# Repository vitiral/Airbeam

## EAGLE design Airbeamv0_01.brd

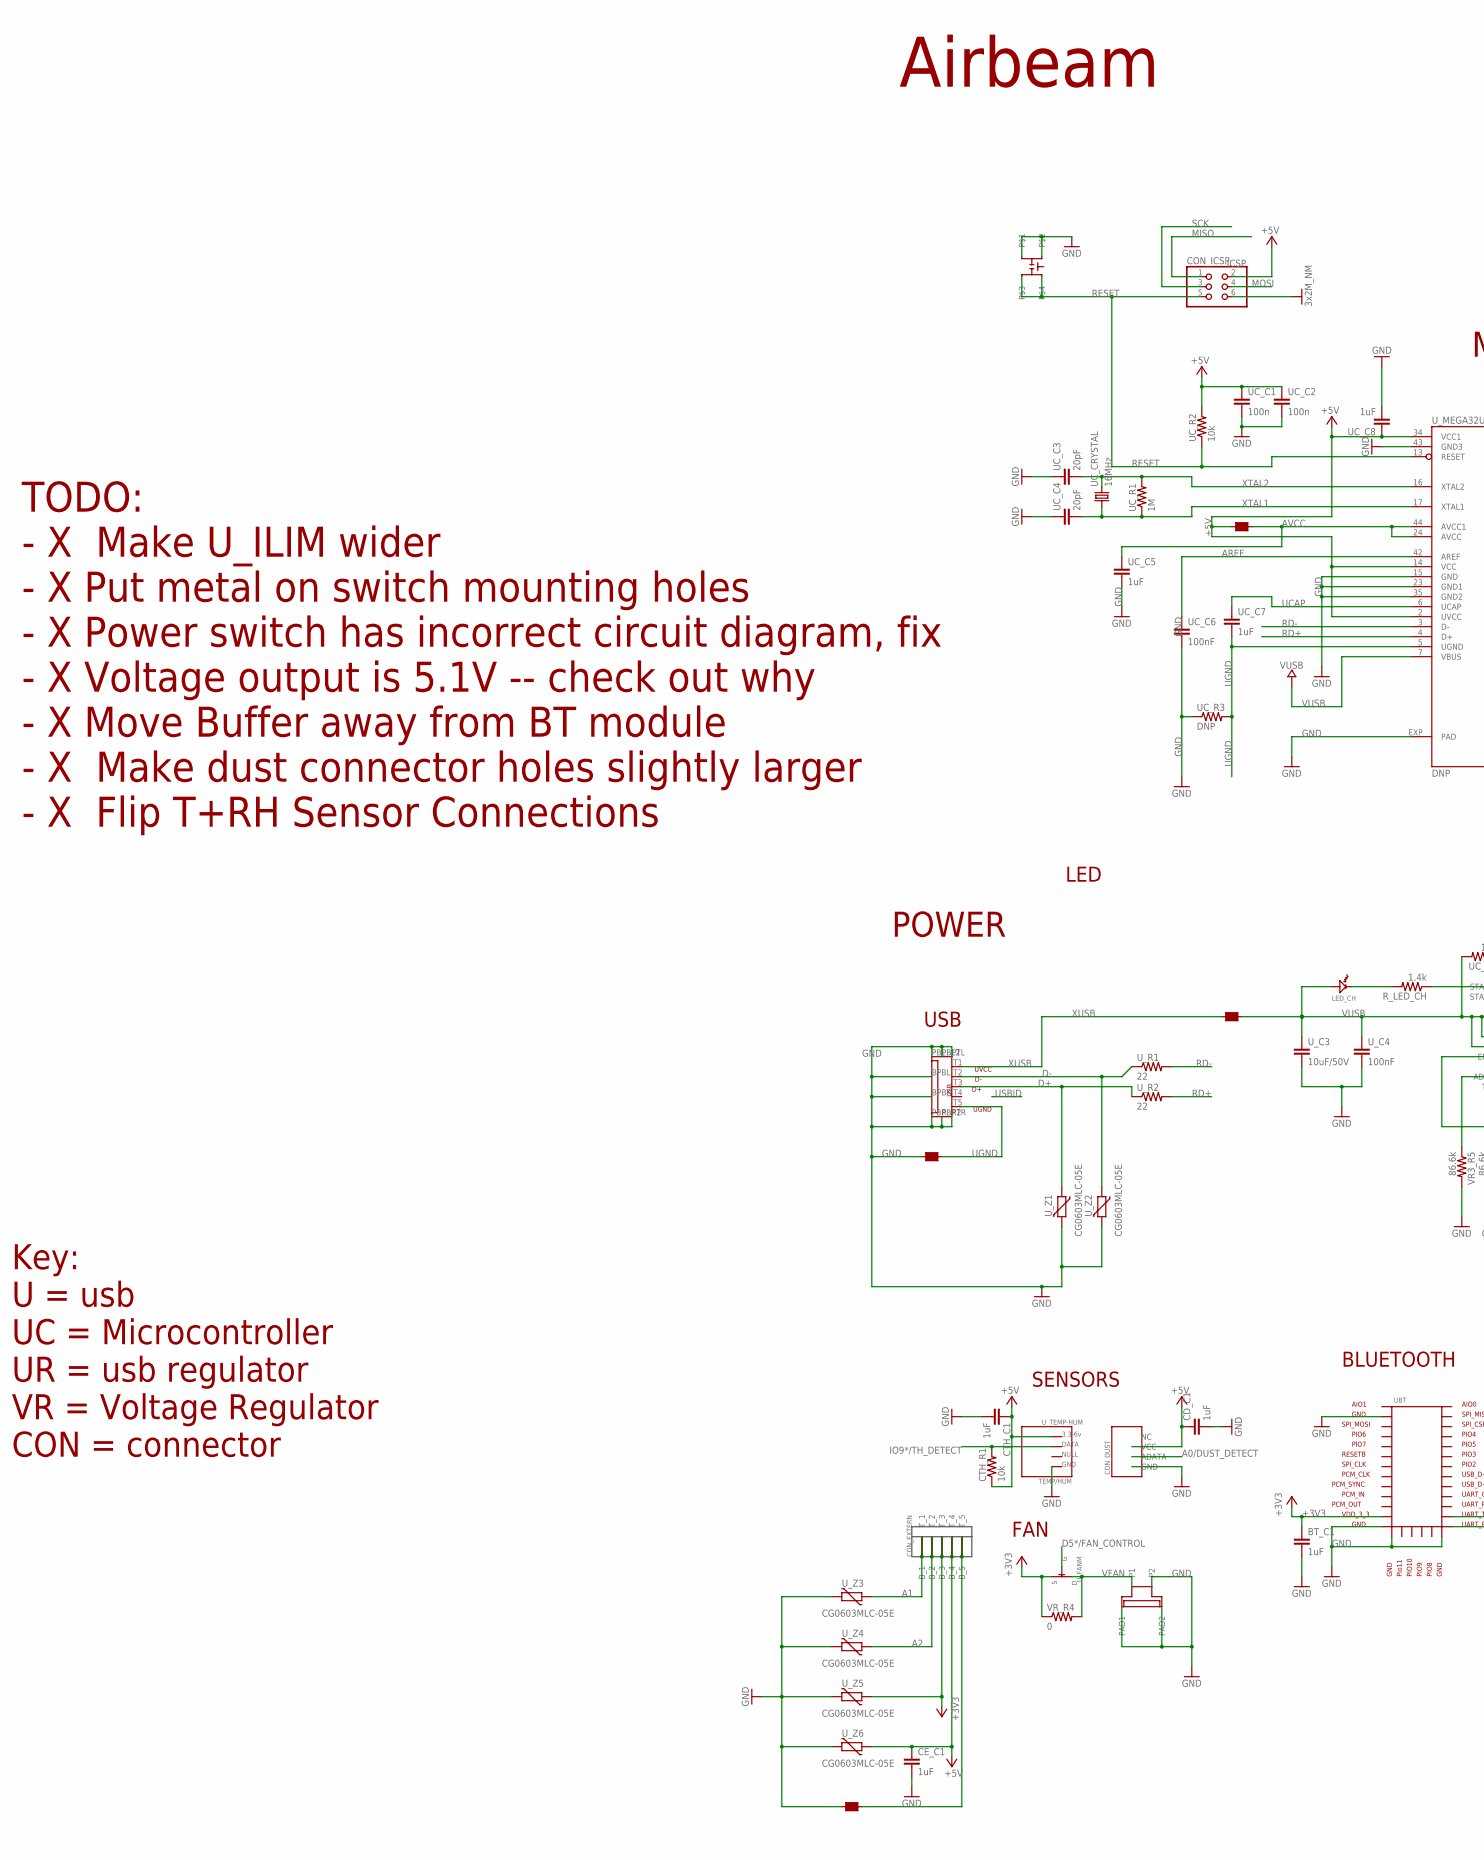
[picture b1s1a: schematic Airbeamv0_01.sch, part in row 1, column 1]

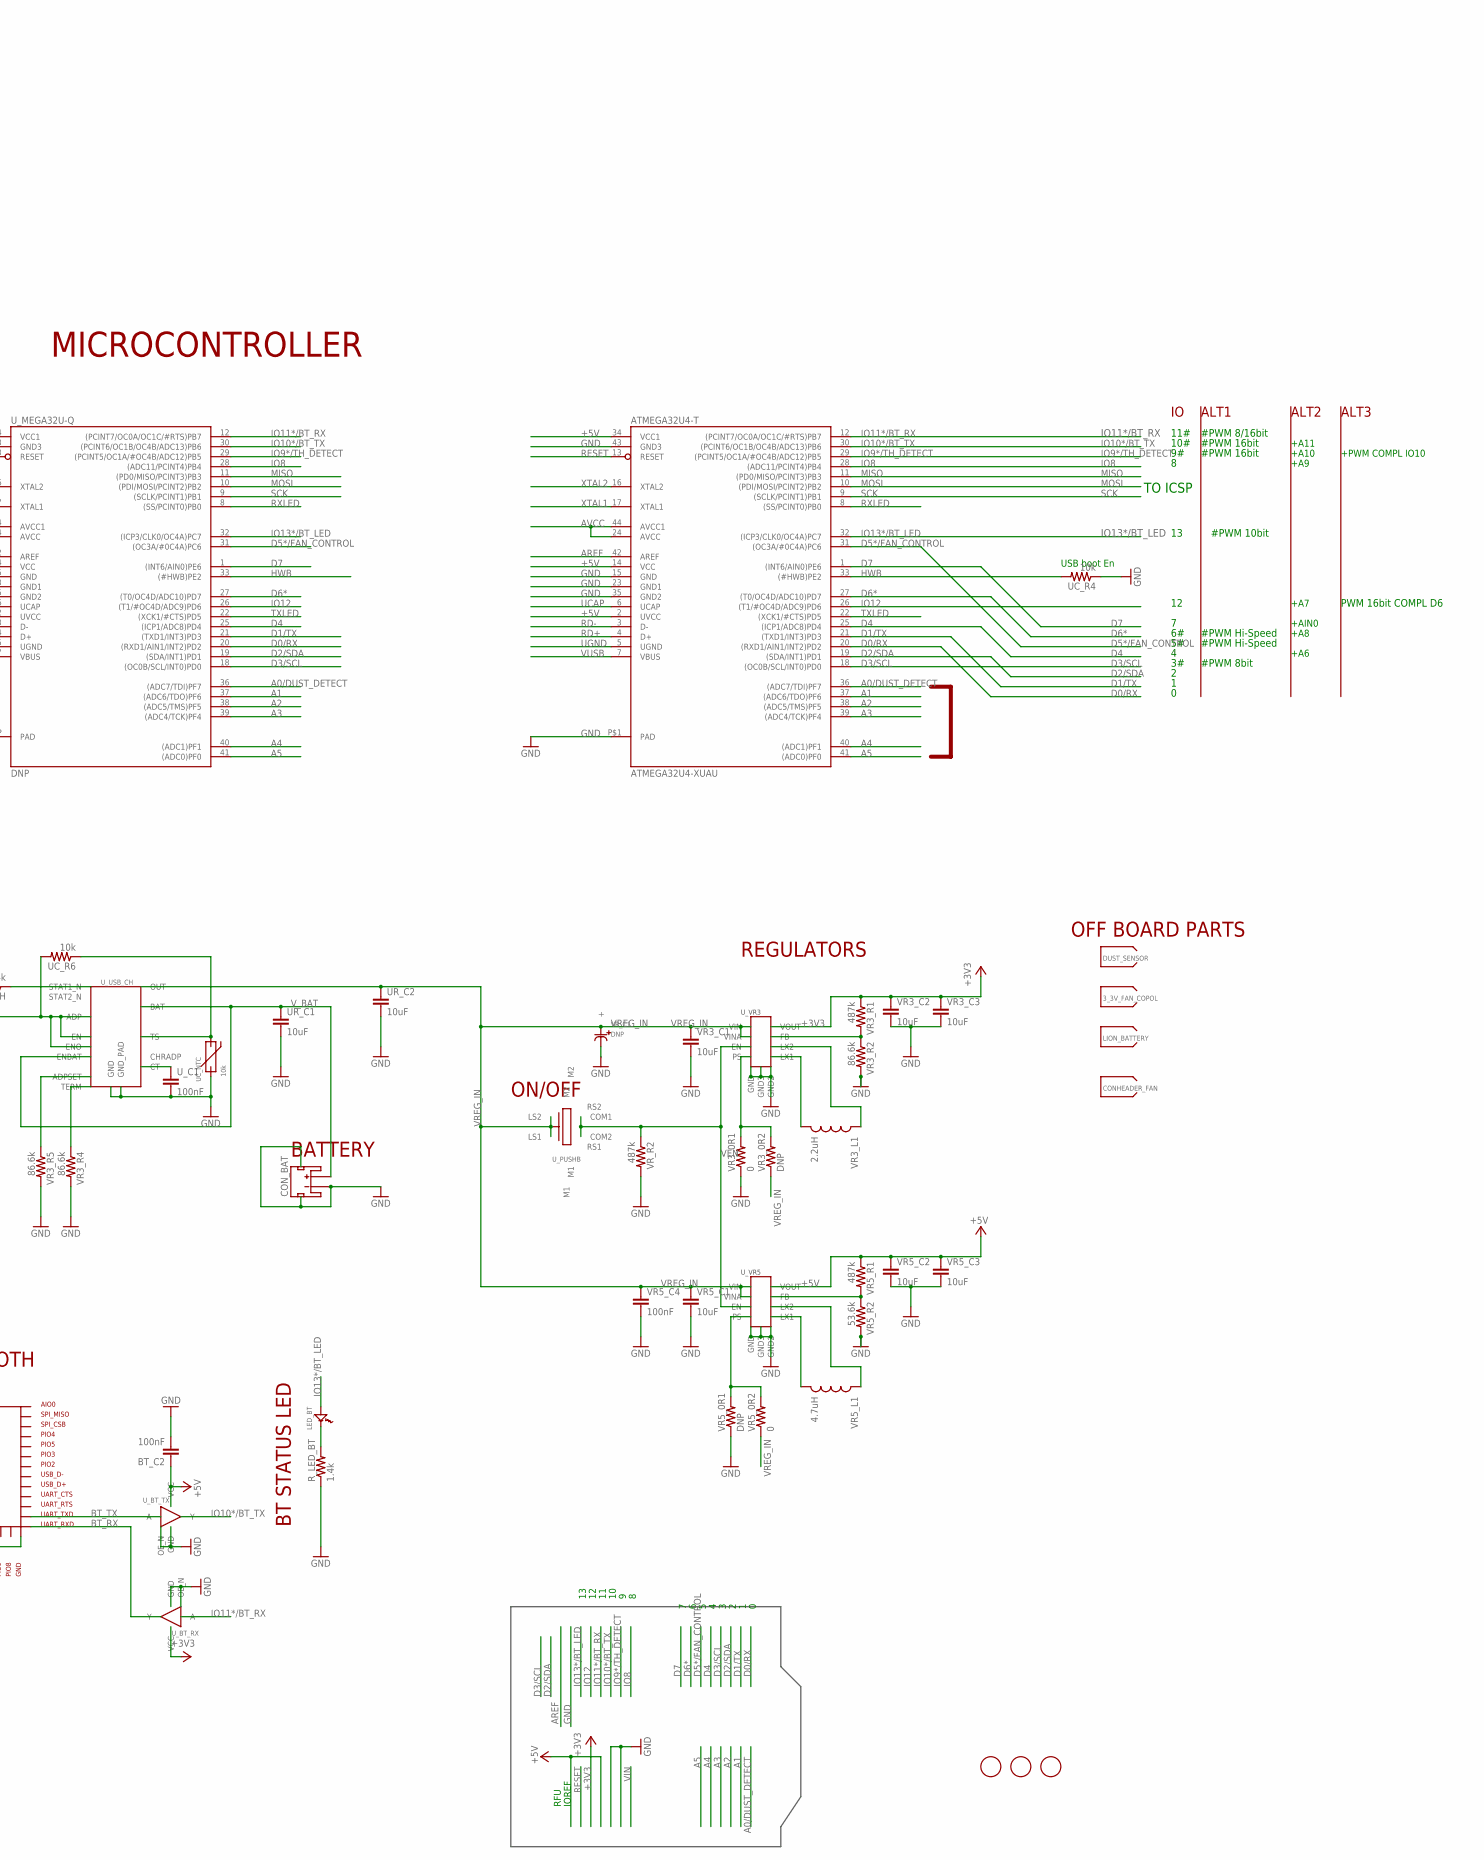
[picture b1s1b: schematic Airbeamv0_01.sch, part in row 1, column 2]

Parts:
3_3V_FAN_COPOL: OFF_BOARD; EMPTY; PARTNO F16FB-05LLC/E
ATMEGA32U4-T: ATMEGA32U4-XUAU; TQFP44-PAD; PARTNO ATMEGA32U4-AU
BT_C1: 1uF; 0603-CAP; PARTNO C1608X5R1C105K080AA
BT_C2: 100nF; 0603-CAP; PARTNO C1608X7R1E104K080AA
CA_FB1: FERITE_BEAD; U_FB1; PARTNO MH2029-600Y
CD_C1: 1uF; 0603-CAP; PARTNO C1608X5R1C105K080AA
CE_C1: 1uF; 0603-CAP; PARTNO C1608X5R1C105K080AA
CONHEADER_FAN: OFF_BOARD; EMPTY; PARTNO 02SUR-32S
CON_BAT: CON_BAT; JST-2-SMD; PARTNO S2B-PH-SM4-TB(LF)(SN)
CON_DUST: CON_DUST; S4B-EH; PARTNO S4B-EH
CON_EXTERN: TBLOCK_5; PARTNO 1770911
CON_FAN: SUR_2PIN; JST-0.8MM
CON_ICSP: ICSP; 2X03; PARTNO 67997-206HLF
CON_USB: USB-FCI
CTH_C1: 1uF; 0603-CAP; PARTNO C1608X5R1C105K080AA
CTH_R1: 10k; 0603-RES; PARTNO RC0603JR-0710KL
DUST_SENSOR: OFF_BOARD; EMPTY; PARTNO PPD60PV-T2
FID1, FID2, FID3: FIDUCIALMOUNT; FIDUCIA-MOUNT; PARTNO DNP
LED_BT: LED; LED_550; PARTNO 550-1107F
LED_CH: LED; LED_550; PARTNO 550-1307F
LION_BATTERY: OFF_BOARD; EMPTY; PARTNO 585460_2000mAh
RESET_SWITCH: DNP; SWITCH_TACTILE
R_LED_BT: 1.4k; 0603-RES; PARTNO RC0603FR-071K4L
R_LED_CH: 1.4k; 0603-RES; PARTNO RC0603FR-071K4L
UBT: BT-NVC-MDCS42A; BT_NVC-MDCS42A
UC_C1, UC_C2: 100n; 0603-CAP; PARTNO C1608X7R1E104K080AA
UC_C3, UC_C4: 20pF; 0603-CAP; PARTNO CL10C200JB8NNNC
UC_C5, UC_C7, UC_C8: 1uF; 0603-CAP; PARTNO C1608X5R1C105K080AA
UC_C6: 100nF; 0603-CAP; PARTNO C1608X7R1E104K080AA
UC_CRYSTAL: 16MHz; HC49UP; PARTNO ECS-160-20-3X-TR
UC_NTC: 10k; 0402; PARTNO ERT-J0EM103J
UC_R1: 1M; 0603-RES; PARTNO RC0603FR-071ML
UC_R2, UC_R4, UC_R6: 10k; 0603-RES; PARTNO RC0603JR-0710KL
UC_R3: DNP; 0603-RES; PARTNO RC0603JR-070RL
UR_C1, UR_C2: 10uF; 0805; PARTNO C2012X5R1C106K085AC
U_BT_RX: V_BUFFER; SOT23-5
U_BT_TX: V_BUFFER; SOT23-5
U_C1: 100nF; 0603-CAP; PARTNO C1608X7R1E104K080AA
U_C3: 10uF/50V; 1206; PARTNO CL31A106KBHNNNE
U_C4: 100nF; 0603-CAP; PARTNO CC0603ZRY5V9BB104
U_FANM: DNP; SOT23
U_FB1, U_FB2, U_FB3: FERITE_BEAD; U_FB1; PARTNO MH2029-600Y
U_MEGA32U-Q: DNP; QFN44ML7X7; PARTNO ATMEGA32U4-MU
U_PUSHB: PUSHBUTTON
U_R1, U_R2: 22; 0603-RES; PARTNO RC0603JR-0722RL
U_TEMP-HUM: RHT03
U_USB_CH: USB-BATTERY_LOAD; TDFN33-14; PARTNO AAT3672IWO-4.2-1-T1
U_VR3, U_VR5: VREG-RTEC6150; WFDFN-10
U_Z1, U_Z2, U_Z3, U_Z4, U_Z5, U_Z6: CG0603MLC-05E; CT/CN0603; PARTNO CG0603MLC-05E
VR3_0R1, VR5_0R2: 0; 0603-RES; PARTNO RC0603JR-070RL
VR3_0R2, VR5_0R1: DNP; 0603-RES; PARTNO RC0603JR-070RL
VR3_C1, VR3_C2, VR3_C3, VR5_C1, VR5_C2, VR5_C3: 10uF; 0805; PARTNO C2012X5R1C106K085AC
VR3_L1: 2.2uH; 1210; PARTNO BRL3225T2R2M
VR3_R1, VR5_R1: 487k; 0603-RES; PARTNO ERJ-3EKF4873V
VR3_R2, VR3_R4, VR3_R5: 86.6k; 0603-RES; PARTNO ERJ-3EKF8662V
VR5_C4: 100nF; 0603-CAP; PARTNO C1608X7R1E104K080AA
VR5_L1: 4.7uH; 1210; PARTNO CBC3225T4R7MR
VR5_R2: 53.6k; 0603-RES; PARTNO RC0805FR-0753K6L
VR_C1: DNP; 2917_CAP
VR_R2: 487k; 0603-RES; PARTNO ERJ-3EKF4873V
VR_R4: 0; 0603-RES; PARTNO RC0603JR-070RL

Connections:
+3V3: BT_C1.1, CON_EXTERN.B_3, CON_EXTERN.T_3, UBT.P$12, U_BT_RX.5 (VCC), U_FANM.2, U_VR3.P$1 (VOUT), U_Z5.1, VR3_C2.1, VR3_C3.1, VR3_R1.1, VR_R4.1
+5V: ATMEGA32U4-T.2 (UVCC), ATMEGA32U4-T.14 (VCC), ATMEGA32U4-T.34 (VCC1), BT_C2.1, CD_C1.1, CE_C1.1, CON_DUST.P$3 (VCC), CON_EXTERN.B_4, CON_EXTERN.T_4, CON_ICSP.2, CTH_C1.1, CTH_R1.1, UC_C1.1, UC_C2.1, UC_C8.1, UC_R2.2, U_BT_TX.5 (VCC), U_FB2.P$1, U_MEGA32U-Q.2 (UVCC), U_MEGA32U-Q.14 (VCC), U_MEGA32U-Q.34 (VCC1), U_TEMP-HUM.P$1, U_VR5.P$1 (VOUT), U_Z6.1, VR5_C2.1, VR5_C3.1, VR5_R1.1
A0/DUST_DETECT: ATMEGA32U4-T.36 ((ADC7/TDI)PF7), CON_DUST.P$2 (ADATA), U_MEGA32U-Q.36 ((ADC7/TDI)PF7)
A1: ATMEGA32U4-T.37 ((ADC6/TDO)PF6), CON_EXTERN.B_1, CON_EXTERN.T_1, U_MEGA32U-Q.37 ((ADC6/TDO)PF6), U_Z3.1
A2: ATMEGA32U4-T.38 ((ADC5/TMS)PF5), CON_EXTERN.B_2, CON_EXTERN.T_2, U_MEGA32U-Q.38 ((ADC5/TMS)PF5), U_Z4.1
A3: ATMEGA32U4-T.39 ((ADC4/TCK)PF4), U_MEGA32U-Q.39 ((ADC4/TCK)PF4)
A4: ATMEGA32U4-T.40 ((ADC1)PF1), U_MEGA32U-Q.40 ((ADC1)PF1)
A5: ATMEGA32U4-T.41 ((ADC0)PF0), U_MEGA32U-Q.41 ((ADC0)PF0)
AREF: ATMEGA32U4-T.42 (AREF), UC_C6.1, U_MEGA32U-Q.42 (AREF)
AVCC: ATMEGA32U4-T.24 (AVCC), ATMEGA32U4-T.44 (AVCC1), UC_C5.1, U_FB2.P$2, U_MEGA32U-Q.24 (AVCC), U_MEGA32U-Q.44 (AVCC1)
BT_RX: UBT.P$20, U_BT_RX.4 (Y)
BT_TX: UBT.P$21, U_BT_TX.2 (A)
D0/RX: ATMEGA32U4-T.20 ((RXD1/AIN1/INT2)PD2), U_MEGA32U-Q.20 ((RXD1/AIN1/INT2)PD2)
D1/TX: ATMEGA32U4-T.21 ((TXD1/INT3)PD3), U_MEGA32U-Q.21 ((TXD1/INT3)PD3)
D2/SDA: ATMEGA32U4-T.19 ((SDA/INT1)PD1), U_MEGA32U-Q.19 ((SDA/INT1)PD1)
D3/SCL: ATMEGA32U4-T.18 ((OC0B/SCL/INT0)PD0), U_MEGA32U-Q.18 ((OC0B/SCL/INT0)PD0)
D4: ATMEGA32U4-T.25 ((ICP1/ADC8)PD4), U_MEGA32U-Q.25 ((ICP1/ADC8)PD4)
D5*/FAN_CONTROL: ATMEGA32U4-T.31 ((OC3A/#0C4A)PC6), U_FANM.1, U_MEGA32U-Q.31 ((OC3A/#0C4A)PC6)
D6*: ATMEGA32U4-T.27 ((T0/OC4D/ADC10)PD7), U_MEGA32U-Q.27 ((T0/OC4D/ADC10)PD7)
D7: ATMEGA32U4-T.1 ((INT6/AIN0)PE6), U_MEGA32U-Q.1 ((INT6/AIN0)PE6)
D+: CON_USB.T3, U_R2.1, U_Z1.1
D-: CON_USB.T2, U_R1.1, U_Z2.1
GND: ATMEGA32U4-T.15 (GND), ATMEGA32U4-T.23 (GND1), ATMEGA32U4-T.35 (GND2), ATMEGA32U4-T.43 (GND3), ATMEGA32U4-T.P$1 (PAD), BT_C1.2, BT_C2.2, CA_FB1.P$1, CD_C1.2, CE_C1.2, CON_BAT.1 (-), CON_BAT.NC1 (PAD1), CON_BAT.NC2 (PAD2), CON_DUST.P$1 (GND), CON_FAN.P2, CON_FAN.PAD1, CON_FAN.PAD2, CON_ICSP.6, CON_USB.BPBL, CON_USB.BPBR, CON_USB.PBL, CON_USB.PBL2, CON_USB.PBR, CON_USB.PBR2, CON_USB.PTL, CON_USB.PTR, CTH_C1.2, RESET_SWITCH.P1, RESET_SWITCH.P2, R_LED_BT.1, UBT.P$2, UBT.P$13, UBT.P$14, UBT.P$19, UC_C1.2, UC_C2.2, UC_C3.1, UC_C4.1, UC_C5.2, UC_C6.2, UC_C8.2, UC_NTC.1, UC_R3.1, UC_R4.1, UR_C1.2, UR_C2.2, U_BT_RX.1 (OE_N), U_BT_RX.3 (GND), U_BT_TX.1 (OE_N), U_BT_TX.3 (GND), U_C1.2, U_C3.2, U_C4.2, U_FB1.P$1, U_MEGA32U-Q.15 (GND), U_MEGA32U-Q.23 (GND1), U_MEGA32U-Q.35 (GND2), U_MEGA32U-Q.43 (GND3), U_MEGA32U-Q.EXP (PAD), U_TEMP-HUM.P$4, U_USB_CH.GND_PAD, U_USB_CH.P$4 (GND), U_VR3.MID_PAD (GND3), U_VR3.P$3 (GND), U_VR3.P$9 (GND2), U_VR5.MID_PAD (GND3), U_VR5.P$3 (GND), U_VR5.P$9 (GND2), U_Z1.2, U_Z2.2, U_Z3.2, U_Z4.2, U_Z5.2, U_Z6.2, VR3_0R1.1, VR3_C1.2, VR3_C2.2, VR3_C3.2, VR3_R2.2, VR3_R4.2, VR3_R5.2, VR5_0R1.1, VR5_C1.2, VR5_C2.2, VR5_C3.2, VR5_C4.2, VR5_R2.2, VR_C1.T- (-), VR_R2.2
HWB: ATMEGA32U4-T.33 ((#HWB)PE2), UC_R4.2, U_MEGA32U-Q.33 ((#HWB)PE2)
IO8: ATMEGA32U4-T.28 ((ADC11/PCINT4)PB4), U_MEGA32U-Q.28 ((ADC11/PCINT4)PB4)
IO9*/TH_DETECT: ATMEGA32U4-T.29 ((PCINT5/OC1A/#OC4B/ADC12)PB5), CTH_R1.2, U_MEGA32U-Q.29 ((PCINT5/OC1A/#OC4B/ADC12)PB5), U_TEMP-HUM.P$2
IO10*/BT_TX: ATMEGA32U4-T.30 ((PCINT6/OC1B/OC4B/ADC13)PB6), U_BT_TX.4 (Y), U_MEGA32U-Q.30 ((PCINT6/OC1B/OC4B/ADC13)PB6)
IO11*/BT_RX: ATMEGA32U4-T.12 ((PCINT7/OC0A/OC1C/#RTS)PB7), U_BT_RX.2 (A), U_MEGA32U-Q.12 ((PCINT7/OC0A/OC1C/#RTS)PB7)
IO12: ATMEGA32U4-T.26 ((T1/#OC4D/ADC9)PD6), U_MEGA32U-Q.26 ((T1/#OC4D/ADC9)PD6)
IO13*/BT_LED: ATMEGA32U4-T.32 ((ICP3/CLK0/OC4A)PC7), LED_BT.ANODE (AN), U_MEGA32U-Q.32 ((ICP3/CLK0/OC4A)PC7)
MISO: ATMEGA32U4-T.11 ((PD0/MISO/PCINT3)PB3), CON_ICSP.1, U_MEGA32U-Q.11 ((PD0/MISO/PCINT3)PB3)
MOSI: ATMEGA32U4-T.10 ((PDI/MOSI/PCINT2)PB2), CON_ICSP.4, U_MEGA32U-Q.10 ((PDI/MOSI/PCINT2)PB2)
unnamed: U_VR3.P$2 (LX2), VR3_L1.1
unnamed: U_USB_CH.P$10 (TERM), VR3_R4.1
unnamed: LED_BT.CATHODE (CATH), R_LED_BT.2
unnamed: U_VR3.P$10 (FB), VR3_R1.2, VR3_R2.1
unnamed: UC_NTC.2, UC_R6.1, U_USB_CH.P$11 (TS)
unnamed: U_C1.1, U_USB_CH.P$14 (CT)
unnamed: CA_FB1.P$2, CON_EXTERN.B_5, CON_EXTERN.T_5
unnamed: R_LED_CH.1, U_USB_CH.P$3 (STAT1_N)
unnamed: U_VR3.P$4 (LX1), VR3_L1.2
unnamed: U_VR5.P$10 (FB), VR5_R1.2, VR5_R2.1
unnamed: U_VR5.P$2 (LX2), VR5_L1.1
unnamed: U_VR5.P$4 (LX1), VR5_L1.2
unnamed: LED_CH.CATHODE (CATH), R_LED_CH.2
unnamed: U_USB_CH.P$1 (ADPSET), VR3_R5.1
RD+: ATMEGA32U4-T.4 (D+), U_MEGA32U-Q.4 (D+), U_R2.2
RD-: ATMEGA32U4-T.3 (D-), U_MEGA32U-Q.3 (D-), U_R1.2
RESET: ATMEGA32U4-T.13 (RESET), CON_ICSP.5, RESET_SWITCH.P3, RESET_SWITCH.P4, UC_R2.1, U_MEGA32U-Q.13 (RESET)
RXLED: ATMEGA32U4-T.8 ((SS/PCINT0)PB0), U_MEGA32U-Q.8 ((SS/PCINT0)PB0)
SCK: ATMEGA32U4-T.9 ((SCLK/PCINT1)PB1), CON_ICSP.3, U_MEGA32U-Q.9 ((SCLK/PCINT1)PB1)
TXLED: ATMEGA32U4-T.22 ((XCK1/#CTS)PD5), U_MEGA32U-Q.22 ((XCK1/#CTS)PD5)
UCAP: ATMEGA32U4-T.6 (UCAP), UC_C7.1, U_MEGA32U-Q.6 (UCAP)
UGND: ATMEGA32U4-T.5 (UGND), CON_USB.T5, UC_C7.2, UC_R3.2, U_FB1.P$2, U_MEGA32U-Q.5 (UGND)
VEN: U_PUSHB.C1 (COM1), U_PUSHB.C2 (COM2), U_VR3.P$6 (EN), U_VR5.P$6 (EN), VR_R2.1
VFAN: CON_FAN.P1, U_FANM.3, VR_R4.2
VR3_PS: U_VR3.P$7 (PS), VR3_0R1.2, VR3_0R2.2
VR5_PS: U_VR5.P$7 (PS), VR5_0R1.2, VR5_0R2.2
VREG_IN: UR_C2.1, U_PUSHB.LS1, U_PUSHB.LS2, U_USB_CH.P$13 (OUT), U_VR3.P$5 (VIN), U_VR3.P$8 (VINA), U_VR5.P$5 (VIN), U_VR5.P$8 (VINA), VR3_0R2.1, VR3_C1.1, VR5_0R2.1, VR5_C1.1, VR5_C4.1, VR_C1.T+ (+)
VUSB: ATMEGA32U4-T.7 (VBUS), LED_CH.ANODE (AN), UC_R6.2, U_C3.1, U_C4.1, U_FB3.P$2, U_MEGA32U-Q.7 (VBUS), U_USB_CH.P$2 (ADP), U_USB_CH.P$6 (EN), U_USB_CH.P$7 (ENO)
V_BAT: CON_BAT.2 (+), UR_C1.1, U_USB_CH.P$8 (ENBAT), U_USB_CH.P$12 (BAT)
XTAL1: ATMEGA32U4-T.17 (XTAL1), UC_C4.2, UC_CRYSTAL.1, UC_R1.1, U_MEGA32U-Q.17 (XTAL1)
XTAL2: ATMEGA32U4-T.16 (XTAL2), UC_C3.2, UC_CRYSTAL.2, UC_R1.2, U_MEGA32U-Q.16 (XTAL2)
XUSB: CON_USB.T1, U_FB3.P$1

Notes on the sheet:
Airbeam
USB boot En
USB
TO ICSP
10#
11#
#PWM 8bit
#PWM Hi-Speed
#PWM 8/16bit
#PWM 16bit
PWM 16bit COMPL D6
#PWM 10bit
+A6
+A7
+A11
+A10
+A8
+A9
+PWM COMPL IO10
+AIN0
ALT1
ALT2
ALT3
SENSORS
TODO: - X Make U_ILIM wider - X Put metal on switch mounting holes - X Power switch has incorrect circuit diagram, fix - X Voltage output is 5.1V -- check out why - X Move Buffer away from BT module - X Make dust connector holes slightly larger - X Flip T+RH Sensor Connections
BATTERY
POWER
Key: U = usb UC = Microcontroller UR = usb regulator VR = Voltage Regulator CON = connector
REGULATORS
ON/OFF
BLUETOOTH
MICROCONTROLLER
FAN
BT STATUS LED
LED
IOREF
RFU
OFF BOARD PARTS

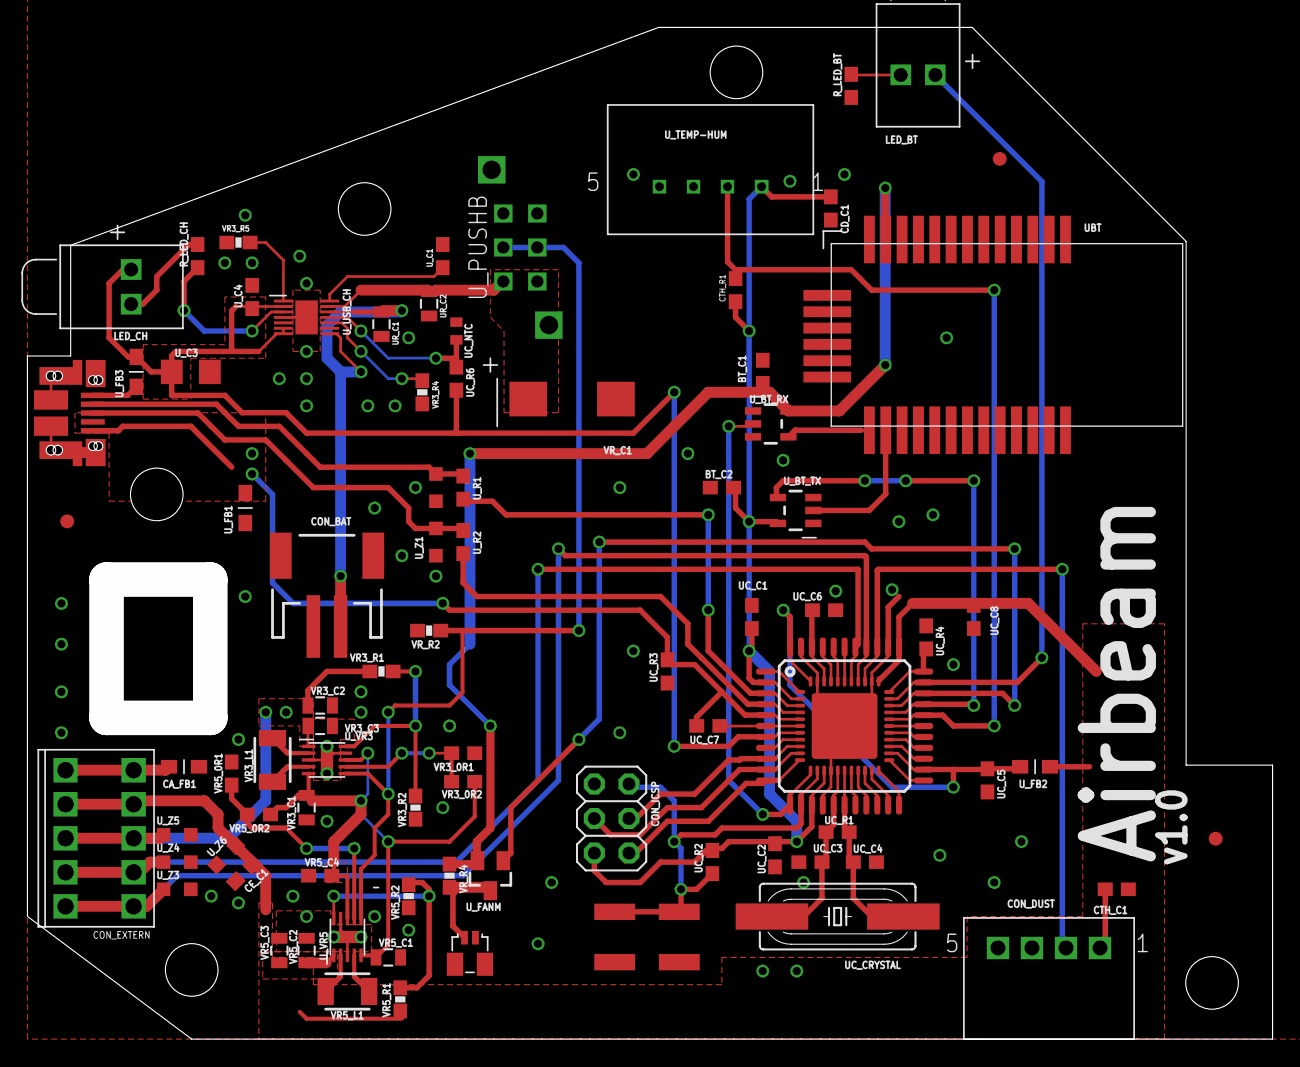
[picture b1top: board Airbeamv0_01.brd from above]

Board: 2 copper layers, 91.4 x 74.3 mm, 90 parts (0 on the bottom side), 64 nets.

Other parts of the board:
U$6: EAGLE_FREESPACE

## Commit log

2014-03-07 First commit, Leonardo
2014-03-07 rename
2014-03-11 blah
2014-03-11 reset to leonardo
2014-03-11 some text
2014-03-11 removing useless stuff
2014-03-12 Added some devices
2014-03-12 preliminary design, waiting for response to questions
2014-03-23 schematic almost done
2014-03-24 Schematic r1
2014-03-24 added bom and stuff
2014-03-24 final revision 1
2014-03-24 added BOM documents
2014-03-24 re-added the ods document
2014-03-24 r1_1
2014-03-24 updated BOM
2014-03-28 got most parts placed, r2
2014-03-28 50% of board layed out, changes made
2014-03-28 Updated BOM and schematic, still have to do personal full review. Having problems with eagle dru checking. Voltage regulator needs to be replaced
2014-03-29 Board is nearing completion
2014-03-29 BOM exported and schematic checked again. Going to go through it and add prices
2014-03-29 updated prices. All parts (without Dust Sensor) = 0. Also added off-board parts to schematic
2014-03-29 some more bom parts
2014-03-29 got the stray air-wires
2014-03-29 more documentation, moved fiducials
2014-03-30 Added library, updated board and schematic to reduce signal keepout
2014-03-30 Added Airwires, ready for review
2014-03-31 added schematic review document
2014-03-31 done alot of work to get functions to work, don't seem to be working
2014-04-02 Board updated, Gerber added, ready for review
2014-04-02 moved back to better spot
2014-04-02 minor change
2014-04-02 minor issue with solder fill, fixed
2014-04-02 added cutout
2014-04-02 dxf updated
2014-04-02 updated pdf and dxf
2014-04-04 did Dave's final updates
2014-04-06 updated per email
2014-04-06 added fan connector
2014-04-06 committing before script
2014-04-06 updated Gerber
2014-04-07 changed to Chris's new cutout
2014-04-07 generated dxf
2014-04-07 Final version! We are ordering this one!
2014-04-07 Final version! We are ordering this one! 1
2014-04-07 added BOM files
2014-04-07 Ordering this board (not the other one)
2014-04-07 ordering with OSHpark (no Gerber needed)
2014-04-07 adjusted cutouts, per OSHpark suggestion
2014-04-07 udated stop mask to correct widths (at least 5mils)
2014-04-07 minor silkscreen problem
2014-04-07 changed bead to one in stock
2014-04-07 updated parts, haven't updated BOM
2014-05-08 Fixed Switch issue, updating voltage choosing issue
2014-05-09 removed most usb + battery chips and replaced with single chip
2014-05-09 added documentation
2014-05-12 updated according to Daves suggestions
2014-05-13 updated bom, added ferrite bead
2014-05-13 updated BOM location, removed uneeded pdf files
2014-05-13 added README for Gerber
2014-05-13 minor changes to schematic
2014-05-19 updating for ordering
2014-05-22 BOM updated, board outline modified for cheaper version (per Chris), FINAL
2014-08-14 added arduino libraries
2014-08-20 committing final items

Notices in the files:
parts and their libraries:
SparkFun-FreqCtrl: Licensing: Creative Commons ShareAlike 4.0 International - https://creativecommons.org/licenses/by-sa/4.0
